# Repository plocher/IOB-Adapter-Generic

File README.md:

# IOB-Adapter-Generic
## License: CERN Open Hardware Licence v1.2

IOB Personality: Generic I/O

A 5x2 plug in that exposes the I2C Expander pins to the IOB board connector

*  Optional:  There are pads for adding an inline resistor to facilitate driving LEDs directly freom the expander.  Their use requires traces (marked on board) to be cut.

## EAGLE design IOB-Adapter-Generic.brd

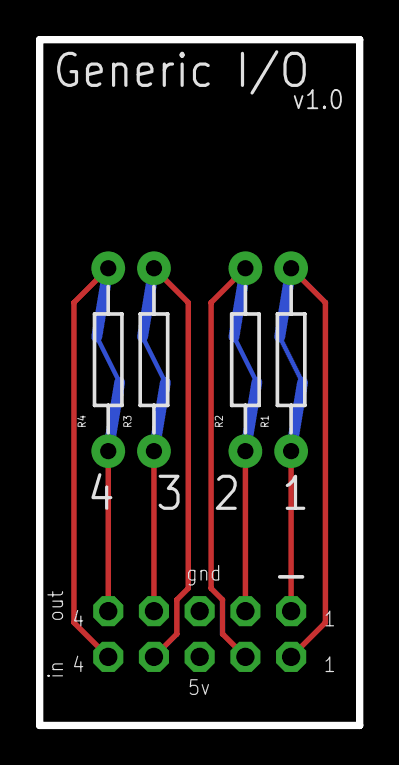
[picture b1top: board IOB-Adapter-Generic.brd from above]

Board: 2 copper layers, 17.8 x 38.1 mm, 5 parts (1 on the bottom side), 8 nets.

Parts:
JP1: CONNECTOR-M05X2; IOB-V3-MODULE
R1, R2, R3, R4: NOSTUFF; CUT-R

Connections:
unnamed: JP1.1, R1.P2
unnamed: JP1.3, R2.P2
unnamed: JP1.7, R3.P2
unnamed: JP1.9, R4.P2
P1: JP1.2, R1.P1
P2: JP1.4, R2.P1
P3: JP1.8, R3.P1
P4: JP1.10, R4.P1

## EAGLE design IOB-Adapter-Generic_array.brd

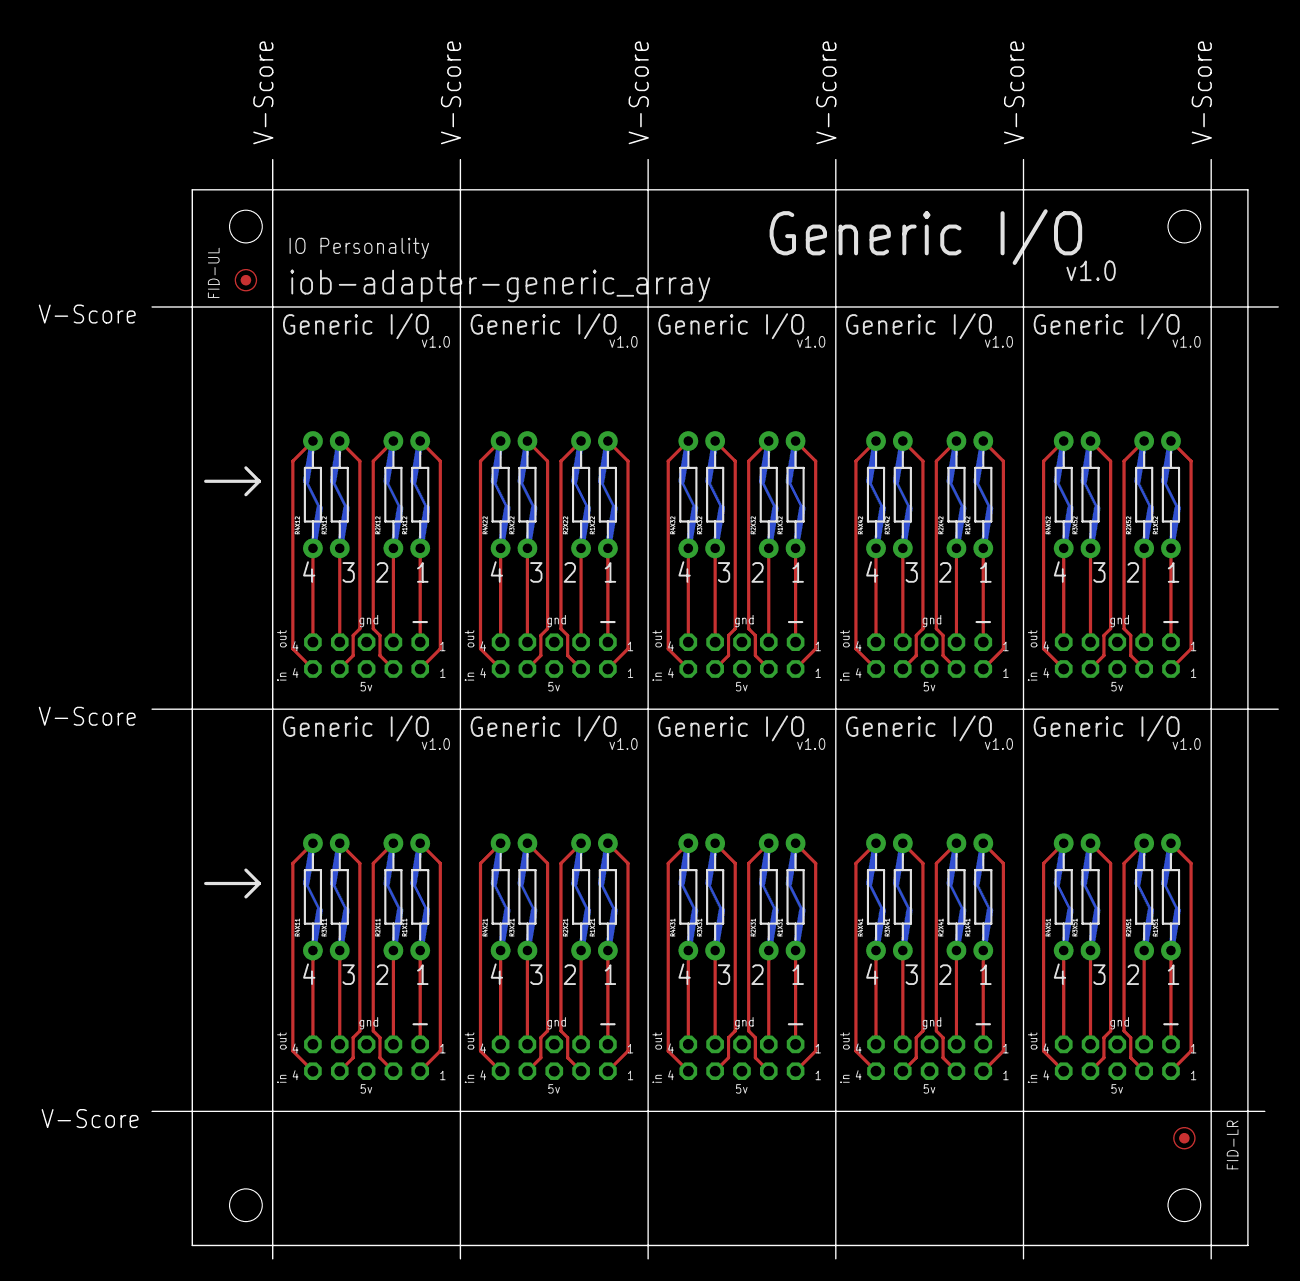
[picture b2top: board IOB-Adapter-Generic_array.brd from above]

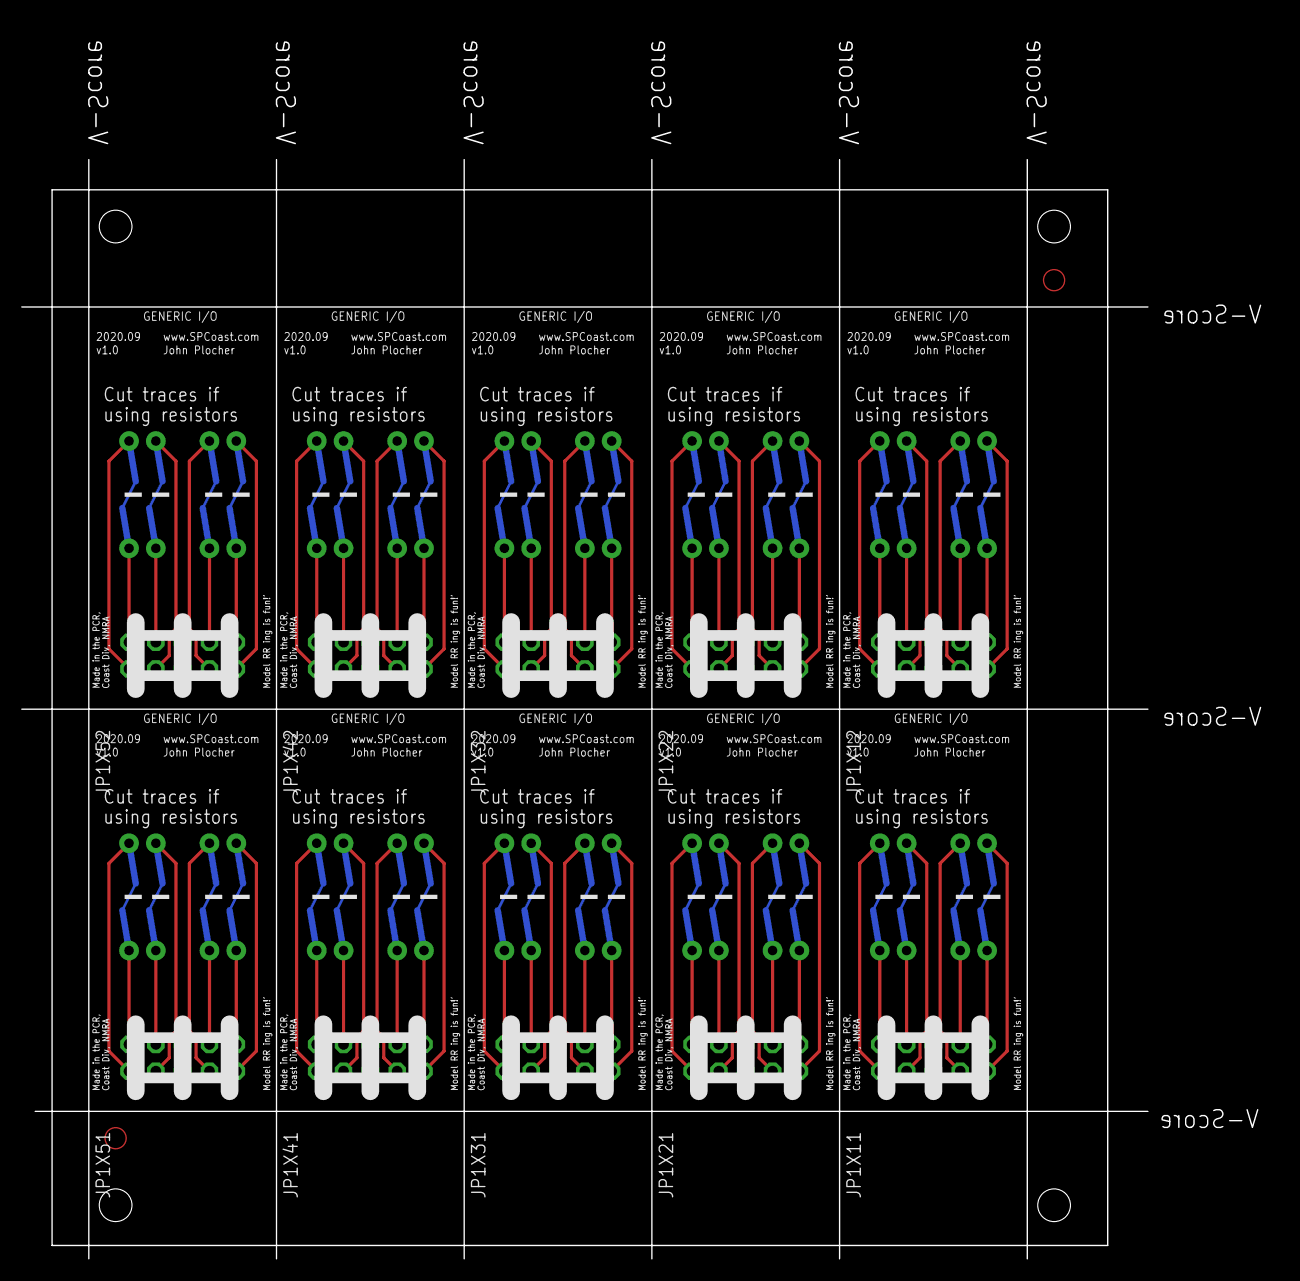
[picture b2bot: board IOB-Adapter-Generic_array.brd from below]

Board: 2 copper layers, 119.0 x 117.2 mm, 53 parts (10 on the bottom side), 80 nets.

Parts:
CARRIER: BOARD; BOARD-DINRAIL-3.17IN-5X2-IOP
FID-LR: FIDUCIAL; FIDUCIAL_1MM
FID-UL: FIDUCIAL; FIDUCIAL_1MM
JP1X11, JP1X12, JP1X21, JP1X22, JP1X31, JP1X32, JP1X41, JP1X42, JP1X51, JP1X52: CONNECTOR-M05X2; IOB-V3-MODULE
R1X11, R1X12, R1X21, R1X22, R1X31, R1X32, R1X41, R1X42, R1X51, R1X52, R2X11, R2X12, R2X21, R2X22, R2X31, R2X32, R2X41, R2X42, R2X51, R2X52, R3X11, R3X12, R3X21, R3X22, R3X31, R3X32, R3X41, R3X42, R3X51, R3X52, R4X11, R4X12, R4X21, R4X22, R4X31, R4X32, R4X41, R4X42, R4X51, R4X52: NOSTUFF; CUT-R

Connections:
unnamed: JP1X11.1, R1X11.P2
unnamed: JP1X12.1, R1X12.P2
unnamed: JP1X21.1, R1X21.P2
unnamed: JP1X22.1, R1X22.P2
unnamed: JP1X31.1, R1X31.P2
unnamed: JP1X32.1, R1X32.P2
unnamed: JP1X41.1, R1X41.P2
unnamed: JP1X42.1, R1X42.P2
unnamed: JP1X51.1, R1X51.P2
unnamed: JP1X52.1, R1X52.P2
unnamed: JP1X11.3, R2X11.P2
unnamed: JP1X12.3, R2X12.P2
unnamed: JP1X21.3, R2X21.P2
unnamed: JP1X22.3, R2X22.P2
unnamed: JP1X31.3, R2X31.P2
unnamed: JP1X32.3, R2X32.P2
unnamed: JP1X41.3, R2X41.P2
unnamed: JP1X42.3, R2X42.P2
unnamed: JP1X51.3, R2X51.P2
unnamed: JP1X52.3, R2X52.P2
unnamed: JP1X11.7, R3X11.P2
unnamed: JP1X12.7, R3X12.P2
unnamed: JP1X21.7, R3X21.P2
unnamed: JP1X22.7, R3X22.P2
unnamed: JP1X31.7, R3X31.P2
unnamed: JP1X32.7, R3X32.P2
unnamed: JP1X41.7, R3X41.P2
unnamed: JP1X42.7, R3X42.P2
unnamed: JP1X51.7, R3X51.P2
unnamed: JP1X52.7, R3X52.P2
unnamed: JP1X11.9, R4X11.P2
unnamed: JP1X12.9, R4X12.P2
unnamed: JP1X21.9, R4X21.P2
unnamed: JP1X22.9, R4X22.P2
unnamed: JP1X31.9, R4X31.P2
unnamed: JP1X32.9, R4X32.P2
unnamed: JP1X41.9, R4X41.P2
unnamed: JP1X42.9, R4X42.P2
unnamed: JP1X51.9, R4X51.P2
unnamed: JP1X52.9, R4X52.P2
P1X11: JP1X11.2, R1X11.P1
P1X12: JP1X12.2, R1X12.P1
P1X21: JP1X21.2, R1X21.P1
P1X22: JP1X22.2, R1X22.P1
P1X31: JP1X31.2, R1X31.P1
P1X32: JP1X32.2, R1X32.P1
P1X41: JP1X41.2, R1X41.P1
P1X42: JP1X42.2, R1X42.P1
P1X51: JP1X51.2, R1X51.P1
P1X52: JP1X52.2, R1X52.P1
P2X11: JP1X11.4, R2X11.P1
P2X12: JP1X12.4, R2X12.P1
P2X21: JP1X21.4, R2X21.P1
P2X22: JP1X22.4, R2X22.P1
P2X31: JP1X31.4, R2X31.P1
P2X32: JP1X32.4, R2X32.P1
P2X41: JP1X41.4, R2X41.P1
P2X42: JP1X42.4, R2X42.P1
P2X51: JP1X51.4, R2X51.P1
P2X52: JP1X52.4, R2X52.P1
P3X11: JP1X11.8, R3X11.P1
P3X12: JP1X12.8, R3X12.P1
P3X21: JP1X21.8, R3X21.P1
P3X22: JP1X22.8, R3X22.P1
P3X31: JP1X31.8, R3X31.P1
P3X32: JP1X32.8, R3X32.P1
P3X41: JP1X41.8, R3X41.P1
P3X42: JP1X42.8, R3X42.P1
P3X51: JP1X51.8, R3X51.P1
P3X52: JP1X52.8, R3X52.P1
P4X11: JP1X11.10, R4X11.P1
P4X12: JP1X12.10, R4X12.P1
P4X21: JP1X21.10, R4X21.P1
P4X22: JP1X22.10, R4X22.P1
P4X31: JP1X31.10, R4X31.P1
P4X32: JP1X32.10, R4X32.P1
P4X41: JP1X41.10, R4X41.P1
P4X42: JP1X42.10, R4X42.P1
P4X51: JP1X51.10, R4X51.P1
P4X52: JP1X52.10, R4X52.P1

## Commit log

2020-09-04 Initial version
2020-09-05 added graphic
2020-09-05 added omnigraffle stencil graphic
2020-09-11 change from edge to PTH mount
2020-09-11 update docs
2020-09-18 silkscreen tweeks
2020-10-05 added values for connectors
2020-10-06 normalized values
